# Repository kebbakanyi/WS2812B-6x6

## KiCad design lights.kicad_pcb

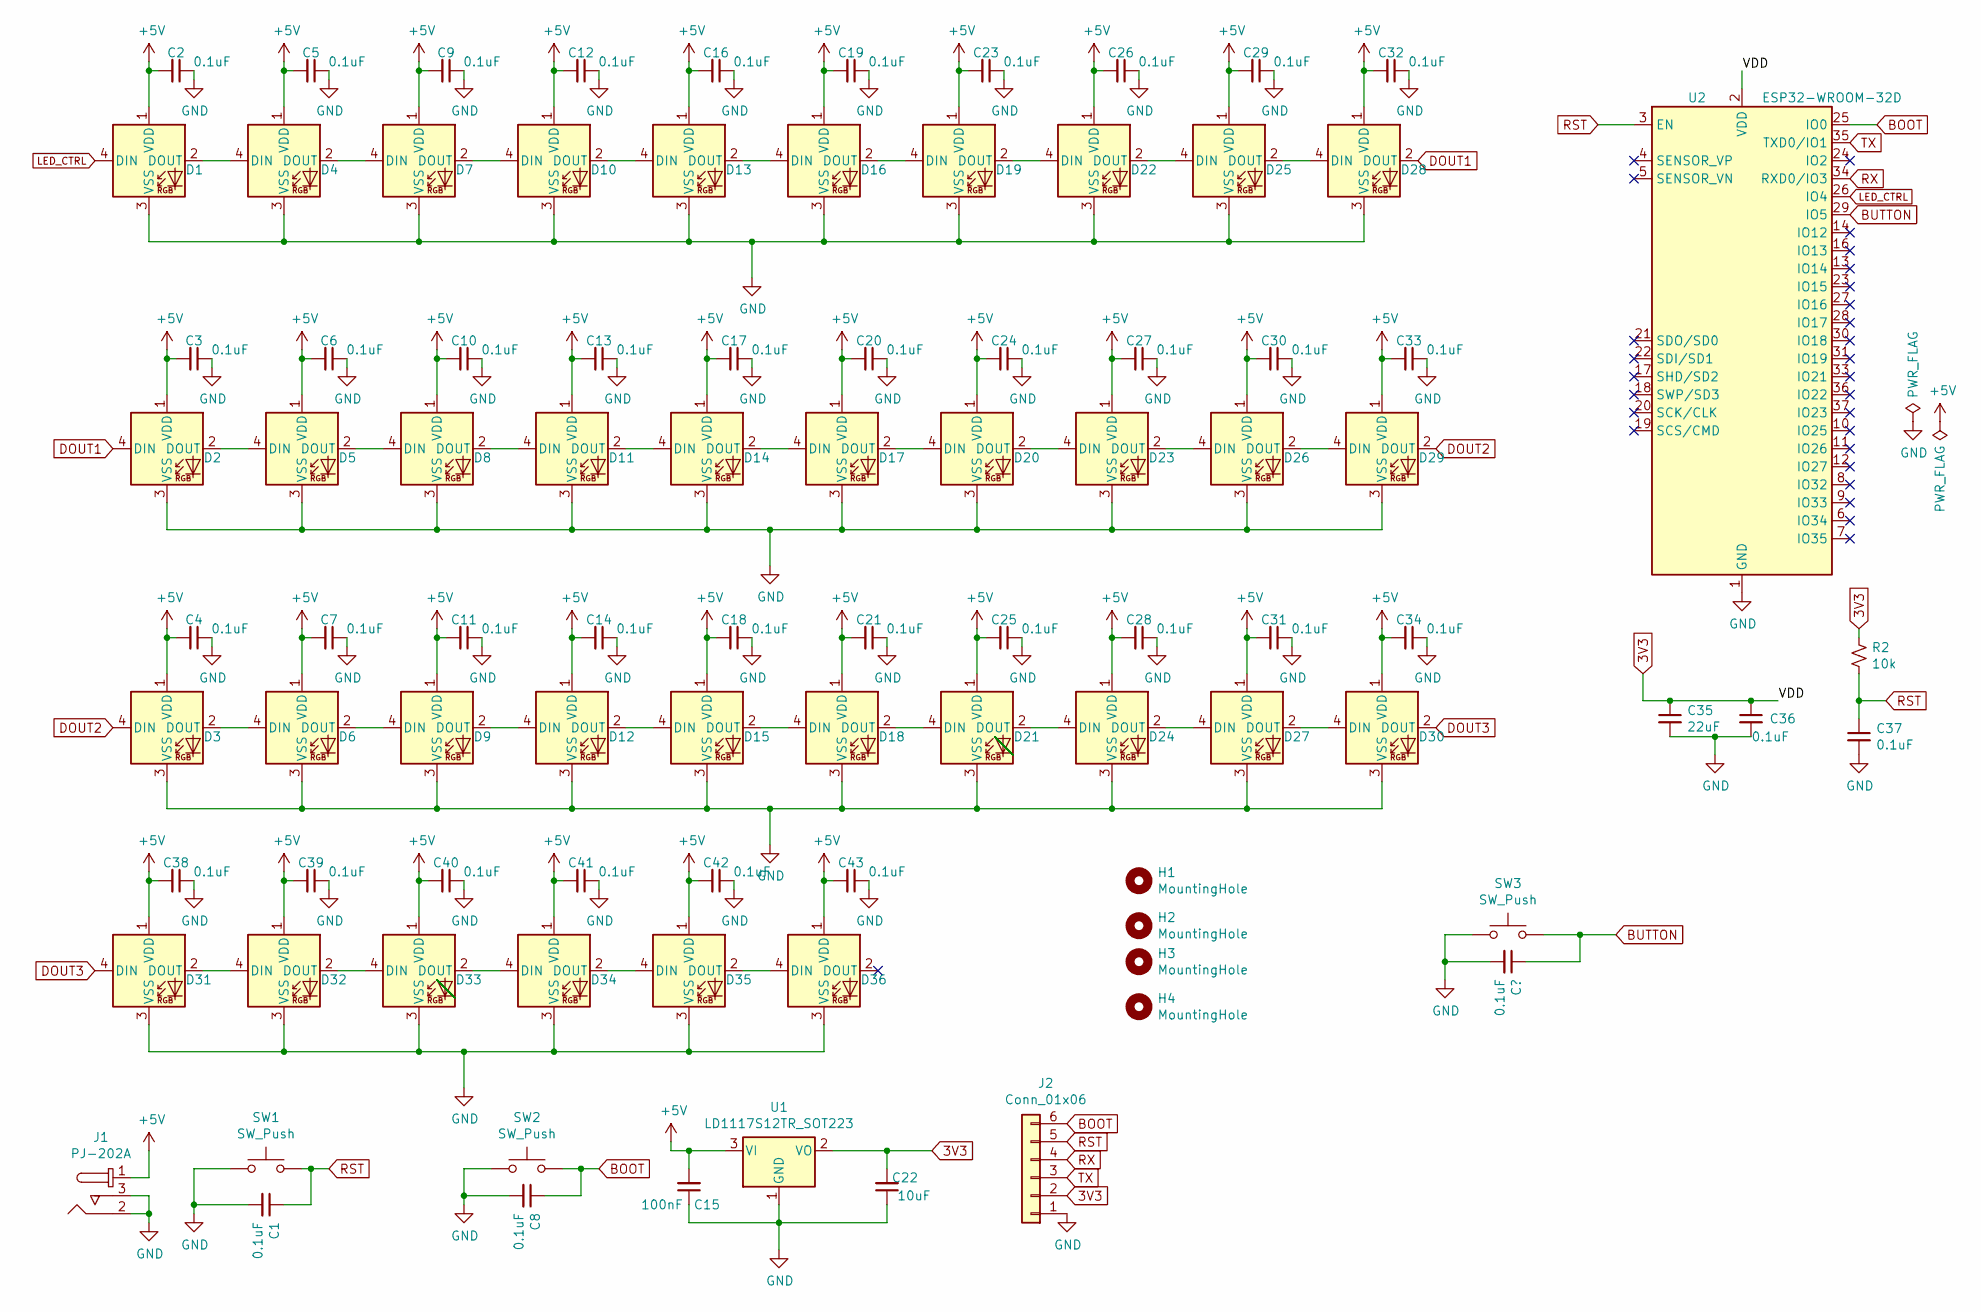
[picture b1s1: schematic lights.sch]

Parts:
C1, C2, C3, C4, C5, C6, C7, C8, C9, C10, C11, C12, C13, C14, C16, C17, C18, C19, C20, C21, C23, C24, C25, C26, C27, C28, C29, C30, C31, C32, C33, C34, C36, C37, C38, C39, C40, C41, C42, C43: 0.1uF; C_0603_1608Metric_Pad1.08x0.95mm_HandSolder
C15: 100nF; C_0603_1608Metric_Pad1.08x0.95mm_HandSolder
C22: 10uF; C_0603_1608Metric_Pad1.08x0.95mm_HandSolder
C35: 22uF; C_0603_1608Metric_Pad1.08x0.95mm_HandSolder
D1, D2, D3, D4, D5, D6, D7, D8, D9, D10, D11, D12, D13, D14, D15, D16, D17, D18, D19, D20, D21, D22, D23, D24, D25, D26, D27, D28, D29, D30, D31, D32, D33, D34, D35, D36: WS2812B; LED_WS2812B_PLCC4_5.0x5.0mm_P3.2mm
H1, H2, H3, H4: MountingHole; MountingHole_2.2mm_M2_Pad_TopOnly
J1: PJ-202A; Barrel_Jack_5.5mmODx2.1mmID_PJ-202A; MPN PJ-202A; Digi-Key_PN CP-202A-ND
J2: Conn_01x06; PinSocket_1x06_P2.54mm_Horizontal
R2: 10k; R_0603_1608Metric_Pad0.98x0.95mm_HandSolder
SW1, SW2, SW3: SW_Push; SW_SPST_B3U-1000P
U1: LD1117S12TR_SOT223; SOT-223-3_TabPin2
U2: ESP32-WROOM-32D; ESP32-WROOM-32

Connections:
3V3: C22.2, C35.1, C36.1, J2.2, R2.1, U1.2 (VO), U2.2 (VDD); also elsewhere on the board
+5V: C2.2, C3.2, C4.2, C5.2, C6.2, C7.2, C9.2, C10.2, C11.2, C12.2, C13.2, C14.2, C15.2, C16.2, C17.2, C18.2, C19.2, C20.2, C21.2, C23.2, C24.2, C25.2, C26.2, C27.2, C28.2, C29.2, C30.2, C31.2, C32.2, C33.2, C34.2, C38.2, C39.2, C40.2, C41.2, C42.2, C43.2, D1.1 (VDD), D2.1 (VDD), D3.1 (VDD), D4.1 (VDD), D5.1 (VDD), D6.1 (VDD), D7.1 (VDD), D8.1 (VDD), D9.1 (VDD), D10.1 (VDD), D11.1 (VDD), D12.1 (VDD), D13.1 (VDD), D14.1 (VDD), D15.1 (VDD), D16.1 (VDD), D17.1 (VDD), D18.1 (VDD), D19.1 (VDD), D20.1 (VDD), D21.1 (VDD), D22.1 (VDD), D23.1 (VDD), D24.1 (VDD), D25.1 (VDD), D26.1 (VDD), D27.1 (VDD), D28.1 (VDD), D29.1 (VDD), D30.1 (VDD), D31.1 (VDD), D32.1 (VDD), D33.1 (VDD), D34.1 (VDD), D35.1 (VDD), D36.1 (VDD), J1.1, U1.3 (VI)
BOOT: C8.1, J2.6, U2.25 (IO0); also elsewhere on the board
BUTTON: SW3.2, U2.29 (IO5); also elsewhere on the board
DOUT1: D2.4 (DIN), D28.2 (DOUT)
DOUT2: D3.4 (DIN), D29.2 (DOUT)
DOUT3: D30.2 (DOUT), D31.4 (DIN)
GND: C1.2, C2.1, C3.1, C4.1, C5.1, C6.1, C7.1, C8.2, C9.1, C10.1, C11.1, C12.1, C13.1, C14.1, C15.1, C16.1, C17.1, C18.1, C19.1, C20.1, C21.1, C22.1, C23.1, C24.1, C25.1, C26.1, C27.1, C28.1, C29.1, C30.1, C31.1, C32.1, C33.1, C34.1, C35.2, C36.2, C37.2, C38.1, C39.1, C40.1, C41.1, C42.1, C43.1, D1.3 (VSS), D2.3 (VSS), D3.3 (VSS), D4.3 (VSS), D5.3 (VSS), D6.3 (VSS), D7.3 (VSS), D8.3 (VSS), D9.3 (VSS), D10.3 (VSS), D11.3 (VSS), D12.3 (VSS), D13.3 (VSS), D14.3 (VSS), D15.3 (VSS), D16.3 (VSS), D17.3 (VSS), D18.3 (VSS), D19.3 (VSS), D20.3 (VSS), D21.3 (VSS), D22.3 (VSS), D23.3 (VSS), D24.3 (VSS), D25.3 (VSS), D26.3 (VSS), D27.3 (VSS), D28.3 (VSS), D29.3 (VSS), D30.3 (VSS), D31.3 (VSS), D32.3 (VSS), D33.3 (VSS), D34.3 (VSS), D35.3 (VSS), D36.3 (VSS), J1.2, J1.3, J2.1, U1.1 (GND), U2.1 (GND), U2.15 (GND), U2.38 (GND), U2.39 (GND); also elsewhere on the board
LED_CTRL: D1.4 (DIN), U2.26 (IO4)
unnamed: D1.2 (DOUT), D4.4 (DIN)
unnamed: D2.2 (DOUT), D5.4 (DIN)
unnamed: D3.2 (DOUT), D6.4 (DIN)
unnamed: D4.2 (DOUT), D7.4 (DIN)
unnamed: D5.2 (DOUT), D8.4 (DIN)
unnamed: D6.2 (DOUT), D9.4 (DIN)
unnamed: D10.2 (DOUT), D13.4 (DIN)
unnamed: D7.2 (DOUT), D10.4 (DIN)
unnamed: D11.2 (DOUT), D14.4 (DIN)
unnamed: D8.2 (DOUT), D11.4 (DIN)
unnamed: D12.2 (DOUT), D15.4 (DIN)
unnamed: D9.2 (DOUT), D12.4 (DIN)
unnamed: D13.2 (DOUT), D16.4 (DIN)
unnamed: D14.2 (DOUT), D17.4 (DIN)
unnamed: D15.2 (DOUT), D18.4 (DIN)
unnamed: D16.2 (DOUT), D19.4 (DIN)
unnamed: D17.2 (DOUT), D20.4 (DIN)
unnamed: D18.2 (DOUT), D21.4 (DIN)
unnamed: D19.2 (DOUT), D22.4 (DIN)
unnamed: D20.2 (DOUT), D23.4 (DIN)
unnamed: D21.2 (DOUT), D24.4 (DIN)
unnamed: D22.2 (DOUT), D25.4 (DIN)
unnamed: D23.2 (DOUT), D26.4 (DIN)
unnamed: D24.2 (DOUT), D27.4 (DIN)
unnamed: D25.2 (DOUT), D28.4 (DIN)
unnamed: D26.2 (DOUT), D29.4 (DIN)
unnamed: D27.2 (DOUT), D30.4 (DIN)
unnamed: D31.2 (DOUT), D32.4 (DIN)
unnamed: D32.2 (DOUT), D33.4 (DIN)
unnamed: D33.2 (DOUT), D34.4 (DIN)
unnamed: D34.2 (DOUT), D35.4 (DIN)
unnamed: D35.2 (DOUT), D36.4 (DIN)
RST: C1.1, C37.1, J2.5, R2.2, U2.3 (EN); also elsewhere on the board
RX: J2.4, U2.34 (RXD0/IO3)
TX: J2.3, U2.35 (TXD0/IO1)

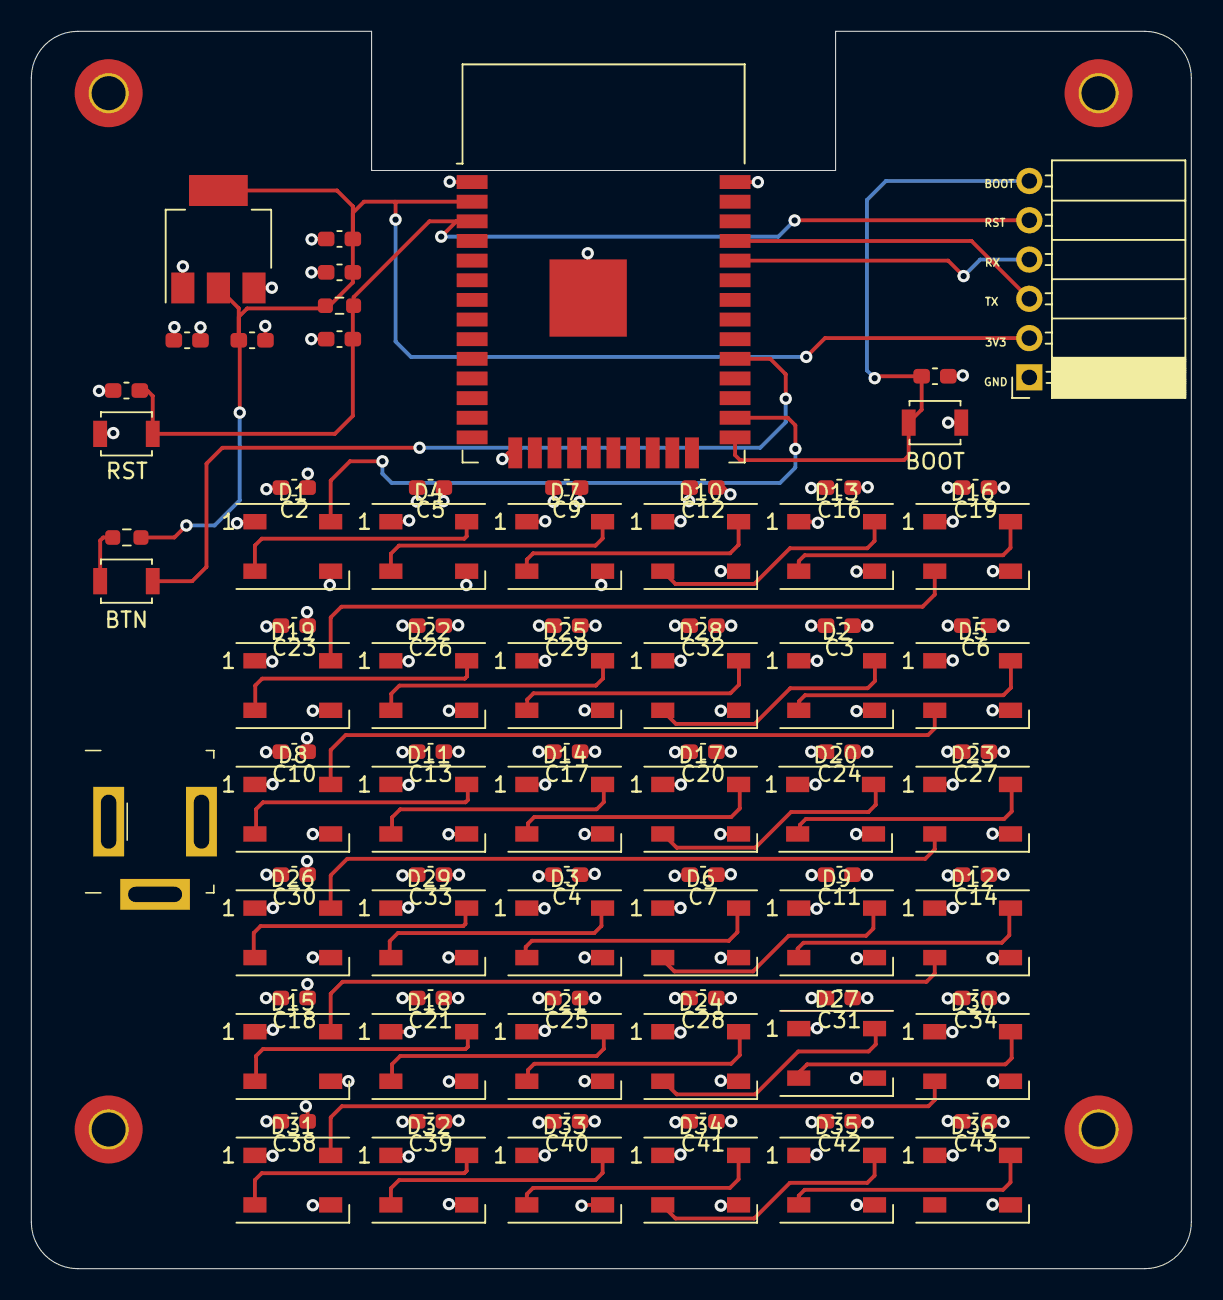
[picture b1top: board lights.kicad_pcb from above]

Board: 4 copper layers, 75.0 x 80.0 mm, 92 parts (0 on the bottom side), 45 nets.

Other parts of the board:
BOOT: SW_Push; SW_SPST_B3U-1000P
BTN: SW_Push; SW_SPST_B3U-1000P
R1: 10k; R_0603_1608Metric_Pad0.98x0.95mm_HandSolder
RST: SW_Push; SW_SPST_B3U-1000P

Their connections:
3V3: R1.2; also elsewhere on the board
BOOT: BOOT.2; also elsewhere on the board
BUTTON: BTN.1; also elsewhere on the board
GND: BOOT.1, RST.1; also elsewhere on the board
unnamed: BTN.2, R1.1
RST: RST.2; also elsewhere on the board
